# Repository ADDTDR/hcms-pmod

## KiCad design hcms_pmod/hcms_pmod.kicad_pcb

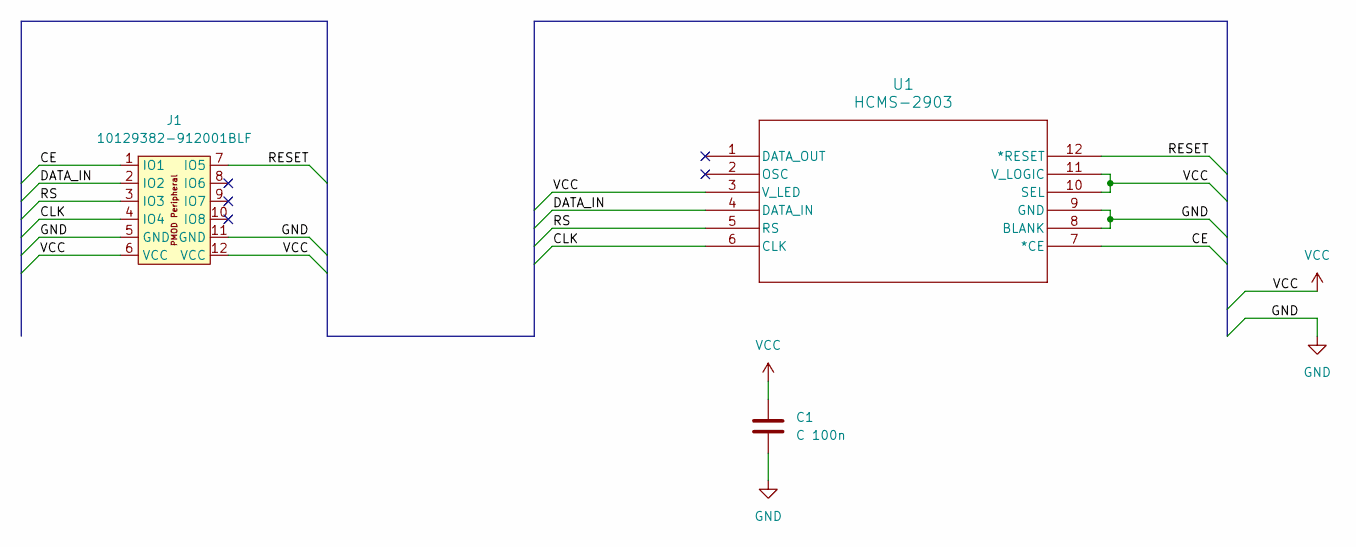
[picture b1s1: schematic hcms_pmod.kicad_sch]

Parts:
C1: C 100n; C_Rect_L4.0mm_W2.5mm_P2.50mm
J1: 10129382-912001BLF; PinHeader_2x06_P2.54mm_PMODPeriph2B; LCSC Part C492434
U1: HCMS-2903; DIP12_HCMS-290X-A_BRA

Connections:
/CE: J1.1 (IO1), U1.7 (*CE)
/CLK: J1.4 (IO4), U1.6 (CLK)
/DATA_IN: J1.2 (IO2), U1.4 (DATA_IN)
/RESET: J1.7 (IO5), U1.12 (*RESET)
/RS: J1.3 (IO3), U1.5 (RS)
GND: C1.2, J1.5 (GND), J1.11 (GND), U1.8 (BLANK), U1.9 (GND)
VCC: C1.1, J1.6 (VCC), J1.12 (VCC), U1.3 (V_LED), U1.10 (SEL), U1.11 (V_LOGIC)

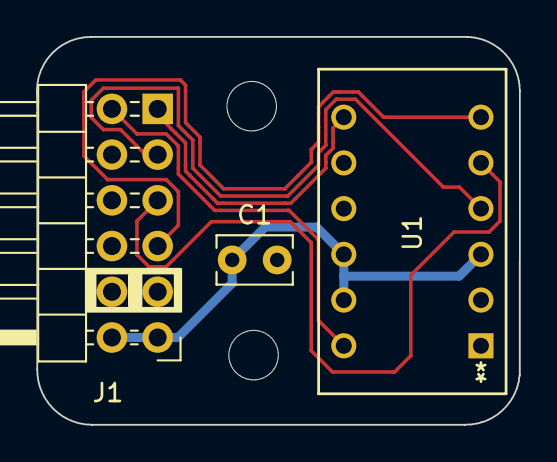
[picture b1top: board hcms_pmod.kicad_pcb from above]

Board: 2 copper layers, 26.8 x 21.5 mm, 3 parts (0 on the bottom side), 7 nets.

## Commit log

2025-09-28 Version 1.0
2025-09-30 Fnish verssion 1
2025-09-30 Add art generate gerbers
